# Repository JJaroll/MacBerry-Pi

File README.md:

# MacBerry Pi G3 · en español

[-9aa0a6?logo=apple&logoColor=white)](docs/guia_macberry_pi.md)

Convierte un **iMac G3 DV (slot loading)** en un equipo moderno: una **Raspberry Pi 5** dentro de la carcasa que usa el **tubo CRT original como monitor VGA**, con sus altavoces y su botón de encendido. Reversible: no hay que cortar nada del iMac.

Este repositorio reúne **la documentación en español**, las **tres placas del proyecto original traducidas**, un **PCB master unificado** que reemplaza el cableado entre ellas, y **visores 3D** (HTML autónomo y STL) para revisarlo todo sin instalar nada.

> **Proyecto original:** [`qbancoffee/imac_g3_ivad_board_init`](https://github.com/qbancoffee/imac_g3_ivad_board_init) (LGPL-3.0), de **Rocky Hill (qbancoffee)**. Este trabajo es derivado de él: ver [CREDITOS.md](CREDITOS.md).

> ⚠️ **Riesgo:** el CRT retiene carga aunque esté desenchufado, el bisel interior es muy frágil y la estática daña la electrónica. Hazlo bajo tu propia responsabilidad.

## Por dónde empezar

**Recomendado:** abre la [**guía interactiva paso a paso**](https://jjaroll.github.io/MacBerry-Pi/) (plan personalizado, cables, jumpers, calibración, diagnóstico y descargas). Los archivos viven en `index.html` y `sitio/`.

O lee los documentos:

1. Lee la [**Guía de cableado con Raspberry Pi 5**](docs/guia_cableado_pi5.md) (pines verificados, jumpers, alimentación y pruebas) y, como contexto, la [guía completa de implementación](docs/guia_macberry_pi.md).
2. Abre los visores de [`visores/`](visores) con doble clic para ver el montaje.
3. Elige el camino de construcción: [placas individuales o PCB master](#placas-individuales-o-master).

## Estructura

```
Macberri Pi/
├─ README.md · CREDITOS.md · LICENSE
├─ docs/
│  ├─ guia_macberry_pi.md              guía completa de implementación (traducción y adaptación)
│  ├─ guia_cableado_pi5.md             cableado, pines verificados, jumpers y pruebas con Pi 5
│  ├─ informe_master_v5.md             informe del PCB master
│  ├─ traducciones/                    README y notas del proyecto original, en español
│  └─ historial/                       informes de versiones anteriores (fusión, v2–v4)
├─ hardware/
│  ├─ placas_individuales/             J20, J22 y Down Converter: KiCad con serigrafía en español y firma,
│  │                                   esquemático_es/ (esquema traducido) y fabricacion/ (Gerber, BOM, iBOM)
│  ├─ master_pcb/                      master v5: KiCad, Gerber, DXF/SVG 1:1, vistas previas
│  └─ contribuciones_rudy/             HAT RPiG3iMac y breakout J20 de Rudy (reng.ca), KiCad + Gerber
├─ firmware/                           Arduino (inicialización IVAD, simulador EDID), init_ivad.py y edid.bin
├─ utilidades/                         ImacG3DVDisplayProperties (calibración de pantalla, Java)
├─ visores/                            HTML autónomos: 3D, cableado sin master, cableado con master, visor STL
├─ stl/
│  ├─ pcb/                             master y placas individuales en STL (1:1, 1,6 mm)
│  ├─ rpi_mount/                       soporte de la Pi (Rudy, reng.ca)
│  └─ bezel/                           bisel interior de Anthony Bernaert (17 STL, CC BY-NC 4.0)
└─ originales/                         de qbancoffee, sin modificar: esquemas PDF, proyecto KiCad (con modelos 3D), imágenes (fotos a 1600 px),
                                       raw_data (capturas I²C y EDID) y surfacemount_version (SMD, en desarrollo)
```

## Visores

| Archivo | Para qué sirve |
|---|---|
| [`visores/visor3d_pcbs.html`](visores/visor3d_pcbs.html) | **Todo en 3D**: master con las 3 placas en sus bolsillos, la Pi 5 con su case, cables cortos, rutas, logos y despiece |
| [`visores/cableado_sin_master.html`](visores/cableado_sin_master.html) | **Sistema de cables sin master**: 19 cables punto a punto entre placas, amplificador y GPIO de la Pi |
| [`visores/cableado_con_master.html`](visores/cableado_con_master.html) | **Sistema con master**: 20 rutas de cobre y cables cortos entre cada bornera y su terminal |
| [`visores/visor_inner_bezel.html`](visores/visor_inner_bezel.html) | **Visor STL del inner bezel (bisel interior)**: las 17 piezas embebidas, ensamblaje, vista explosionada, orden de montaje, cotas, medidas, piezas con soportes sobre la cama y descarga en .zip |

Funcionan con doble clic y sin internet (three.js y los STL van incrustados). Solo las tipografías de algunos visores vienen de Google Fonts; sin conexión se usa la del sistema.

## BOM interactivo (iBOM)

Cada placa tiene su BOM interactivo en español: lista de componentes, posición en la placa (cara frontal y trasera), pistas, zonas y serigrafía. Se abren con doble clic. Colores base: J20 azul, J22 púrpura, Down Converter negro y master verde.

| Placa | iBOM |
|---|---|
| PCB master v5 | [`hardware/master_pcb/ibom_master.html`](hardware/master_pcb/ibom_master.html) |
| J20 · video y ATmega | [`hardware/placas_individuales/J20_video/ibom_es.html`](hardware/placas_individuales/J20_video/ibom_es.html) |
| J22 · frontal y audio | [`hardware/placas_individuales/J22_frontal_audio/ibom_es.html`](hardware/placas_individuales/J22_frontal_audio/ibom_es.html) |
| Down Converter | [`hardware/placas_individuales/DownConverter/ibom_es.html`](hardware/placas_individuales/DownConverter/ibom_es.html) |

Se generan con [`utilidades/generar_ibom/`](utilidades/generar_ibom), sin KiCad. Los iBOM originales (en inglés) siguen en `originales/` y en `fabricacion/bom/`.

## Placas individuales o master

- **Placas individuales** ([`hardware/placas_individuales/`](hardware/placas_individuales)): el diseño original con sus borneras y el cableado de siempre. Es lo más sencillo de fabricar y ensamblar (todo *through-hole*). Serigrafía y comentarios traducidos al español y firma `JJaroll.dev`.
- **PCB master** ([`hardware/master_pcb/`](hardware/master_pcb)): una sola placa con la forma de la placa lógica 820-1131-A. Las 3 placas individuales se atornillan en bolsillos (holgura 0,3 mm) y el master las une con pistas, con huecos para la Raspberry Pi 5 con su case y un módulo PAM8403. Ver [`docs/informe_master_v5.md`](docs/informe_master_v5.md).

**Estado del master:** 20 de 20 conexiones verificadas con script propio y sin cortocircuitos. **No se ha ejecutado DRC en KiCad ni se ha fabricado.** Lee la sección «Antes de fabricar» del informe. Las medidas salen de fotos y de un *cutting mat*: verifica con calibre.

## Qué cambié respecto al original

- Serigrafía y comentarios de las 3 placas traducidos al español (las señales técnicas como `SDA`, `GND`, `MOSI` se mantienen).
- Firma `JJaroll.dev` y créditos en el bloque de título de cada placa.
- Documentación del proyecto original y guía MacBerry Pi (Raspberry Pi 5) en español.
- PCB master, visores, mapas de cableado y STL nuevos.

Las placas individuales incluyen su Gerber en español listo para fabricar (`fabricacion/*_gerber.zip`), con DRC revisado. Los Gerber originales (serigrafía en inglés) siguen en [`originales/proyecto_kicad_original/`](originales/proyecto_kicad_original).

## Contribuir

Issues y pull requests son bienvenidos: errores de traducción, medidas verificadas con calibre, resultados de DRC o fabricación del master.

## Licencia

[LGPL-3.0](LICENSE), igual que el proyecto original. Lo derivado se publica con la misma licencia.

**Excepción:** los STL del bisel interior (`stl/bezel/`) son obra de Anthony Bernaert bajo **[CC BY-NC 4.0](stl/bezel/LICENSE_CC-BY-NC-4.0.md)** (atribución, **solo uso no comercial**) y no están cubiertos por la LGPL. Ver [`stl/bezel/LEEME.md`](stl/bezel/LEEME.md).

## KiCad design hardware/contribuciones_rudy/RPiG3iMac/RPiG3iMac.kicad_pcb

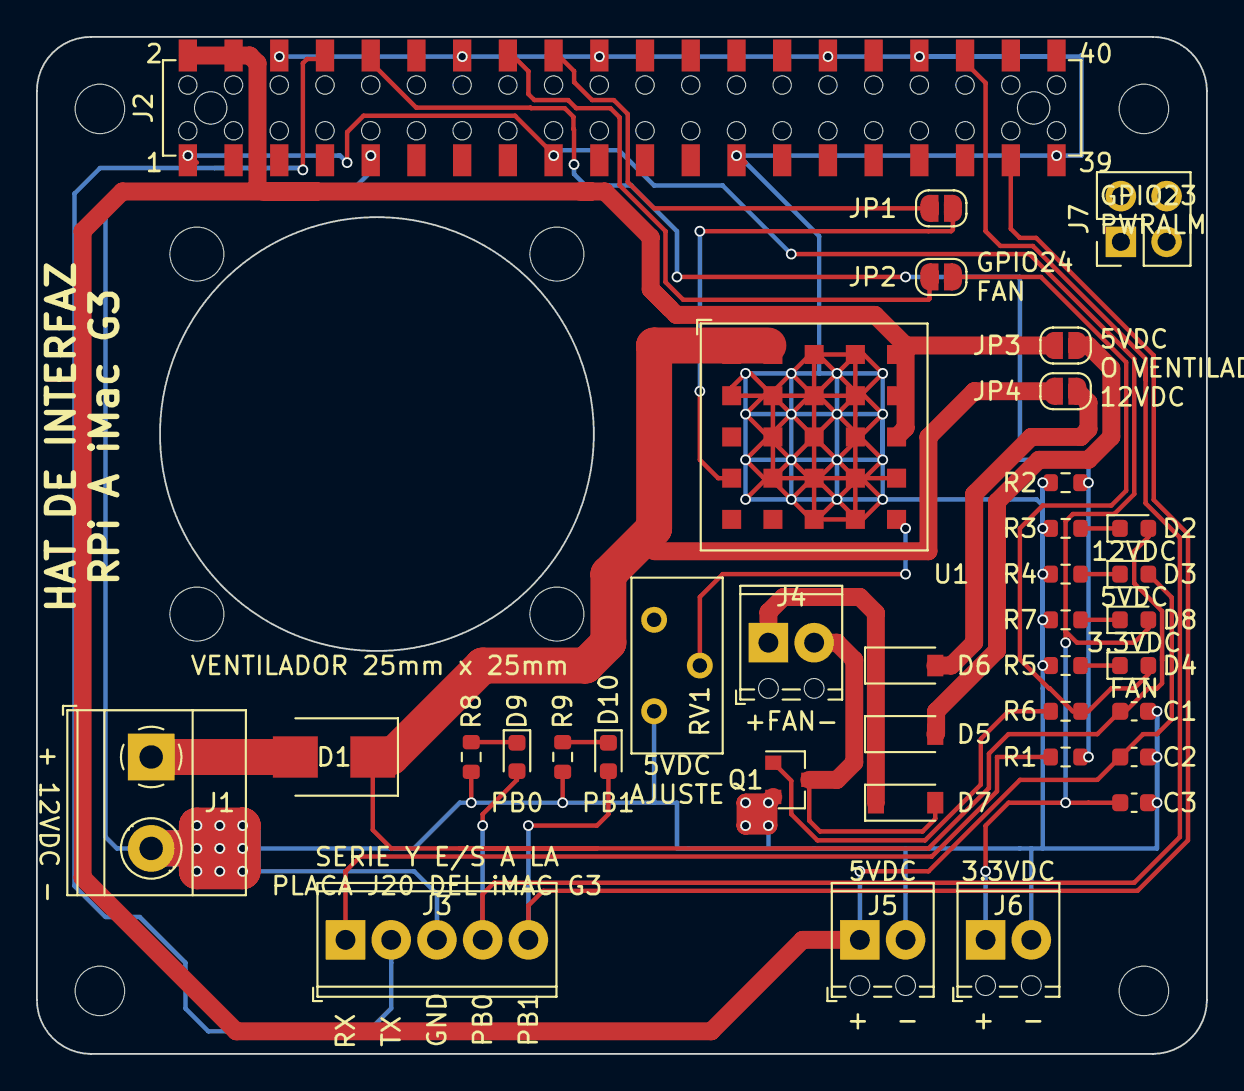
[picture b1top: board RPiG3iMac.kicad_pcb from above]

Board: 2 copper layers, 65.0 x 56.5 mm, 40 parts (0 on the bottom side), 26 nets.

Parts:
 : MountingHole_3mm
 #2,  #3,  #4: MountingHole_3mm
C1: 10uF 25V; C_0603_1608Metric
C2, C3: 22uF 10V; C_0603_1608Metric
D1: 40V 3A; D_SMB
D2: 12VDC; LED_0603_1608Metric
D3: 5VDC; LED_0603_1608Metric
D4: FAN; LED_0603_1608Metric
D5, D6, D7: 100V 150mA; D_SOD-123
D8, D9, D10: 3.3VDC; LED_0603_1608Metric
J1: 12VDC IN; TerminalBlock_Phoenix_MKDS-1,5-2-5.08_1x02_P5.08mm_Horizont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
J2: RPi; Harwin_M20-7812045_2x20_P2.54mm_Vertical_rpi
J3: SERIAL TO iMAC G3 J20 BOARD; TerminalBlock_Phoenix_MPT-0,5-5-2.54_1x05_P2.54mm_Horizontal
J4: FAN; TerminalBlock_Phoenix_MPT-0,5-2-2.54_1x02_P2.54mm_Horizontal
J5: 5VDC OUT; TerminalBlock_Phoenix_MPT-0,5-2-2.54_1x02_P2.54mm_Horizontal
J6: 3.3V DC OUT; TerminalBlock_Phoenix_MPT-0,5-2-2.54_1x02_P2.54mm_Horizontal
J7: RPi POE Header; PinHeader_2x02_P2.54mm_Vertical
JP1: GPIO23 PWR STATUS; SolderJumper-2_P1.3mm_Open_RoundedPad1.0x1.5mm
JP2: GPIO24 TO FAN; SolderJumper-2_P1.3mm_Open_RoundedPad1.0x1.5mm
JP3: 5VDC; SolderJumper-2_P1.3mm_Open_RoundedPad1.0x1.5mm
JP4: 12VDC; SolderJumper-2_P1.3mm_Open_RoundedPad1.0x1.5mm
Q1: BC817; SOT-23
R1: 1K0; R_0603_1608Metric
R2, R3: 2K0; R_0603_1608Metric
R4, R6: 470; R_0603_1608Metric
R5, R7, R8, R9: 220; R_0603_1608Metric
RV1: 5M0; Potentiometer_Bourns_3296Y_Vertical
U1: RPM5.0-3.0; Converter_DCDC_RECOM_RPMx.x-x.0

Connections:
+3V3: C3.1, D8.2, J2.1, J2.17, J6.1
+5V: C2.1, D3.2, J2.2, J2.4, J5.1, JP3.1, U1.A5, U1.B5, U1.C5
+12V: C1.1, D1.1, D2.2, JP4.1, U1.A1, U1.A2
/PB0_FROM_J20: D9.2, J2.36, J3.4
/PB1_FROM_J20: D10.2, J2.37, J3.5
/RX_FROM_J20: J2.8, J3.2
/TX_FROM_J20_(5V): J3.1, R1.1
GND: C1.2, C2.2, C3.2, J1.2, J2.6, J2.9, J2.14, J2.20, J2.25, J2.30, J2.34, J2.39, J3.3, J5.2, J6.2, Q1.2, R2.2, R3.2, R4.2, R5.2, R7.2, R8.2, R9.2, RV1.3, U1.A3, U1.A4, U1.B1, U1.B2, U1.B3, U1.B4, U1.C2, U1.C3, U1.C4, U1.D2, U1.D3, U1.D4, U1.D5, U1.E3, U1.E4
unnamed: D1.2, J1.1
unnamed: D2.1, R3.1
unnamed: D3.1, R4.1
unnamed: D4.1, R5.1
unnamed: D4.2, JP2.1, R6.2
unnamed: D5.1, D6.1, D7.1, J4.1
unnamed: D5.2, JP3.2
unnamed: D6.2, JP4.2
unnamed: D7.2, J4.2, Q1.3
unnamed: D8.1, R7.1
unnamed: D9.1, R8.1
unnamed: D10.1, R9.1
unnamed: J2.10, R1.2, R2.1
unnamed: J2.16, JP2.2
unnamed: J2.18, JP1.2
unnamed: JP1.1, U1.D1
unnamed: Q1.1, R6.1
unnamed: RV1.2, U1.E5

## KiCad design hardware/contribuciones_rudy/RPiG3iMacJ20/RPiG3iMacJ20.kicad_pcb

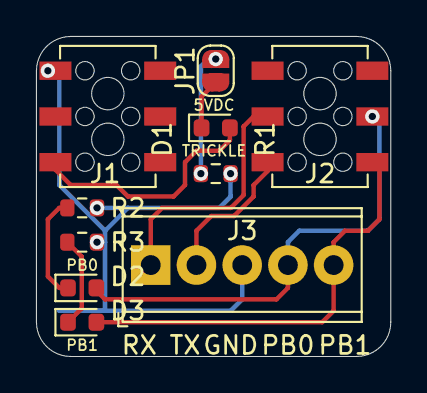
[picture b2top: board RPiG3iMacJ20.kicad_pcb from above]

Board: 2 copper layers, 19.7 x 17.8 mm, 10 parts (0 on the bottom side), 10 nets.

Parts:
D1, D2, D3: LED; LED_0603_1608Metric
J1, J2: Conn_02x03_Odd_Even; Harwin_M20-7810345_2x03_P2.54mm_Vertical
J3: Screw_Terminal_01x05; TerminalBlock_Phoenix_MPT-0,5-5-2.54_1x05_P2.54mm_Horizontal
JP1: SolderJumper_2_Open; SolderJumper-2_P1.3mm_Open_RoundedPad1.0x1.5mm
R1: 470; R_0603_1608Metric
R2, R3: 220; R_0603_1608Metric

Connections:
+5V: D1.2, J1.5
GND: J1.1, J3.3, R1.2, R2.2, R3.2
unnamed: D1.1, JP1.1
unnamed: D2.1, R2.1
unnamed: D2.2, J2.4, J3.4
unnamed: D3.1, R3.1
unnamed: D3.2, J2.6, J3.5
unnamed: J2.3, J3.1
unnamed: J2.5, J3.2
unnamed: JP1.2, R1.1

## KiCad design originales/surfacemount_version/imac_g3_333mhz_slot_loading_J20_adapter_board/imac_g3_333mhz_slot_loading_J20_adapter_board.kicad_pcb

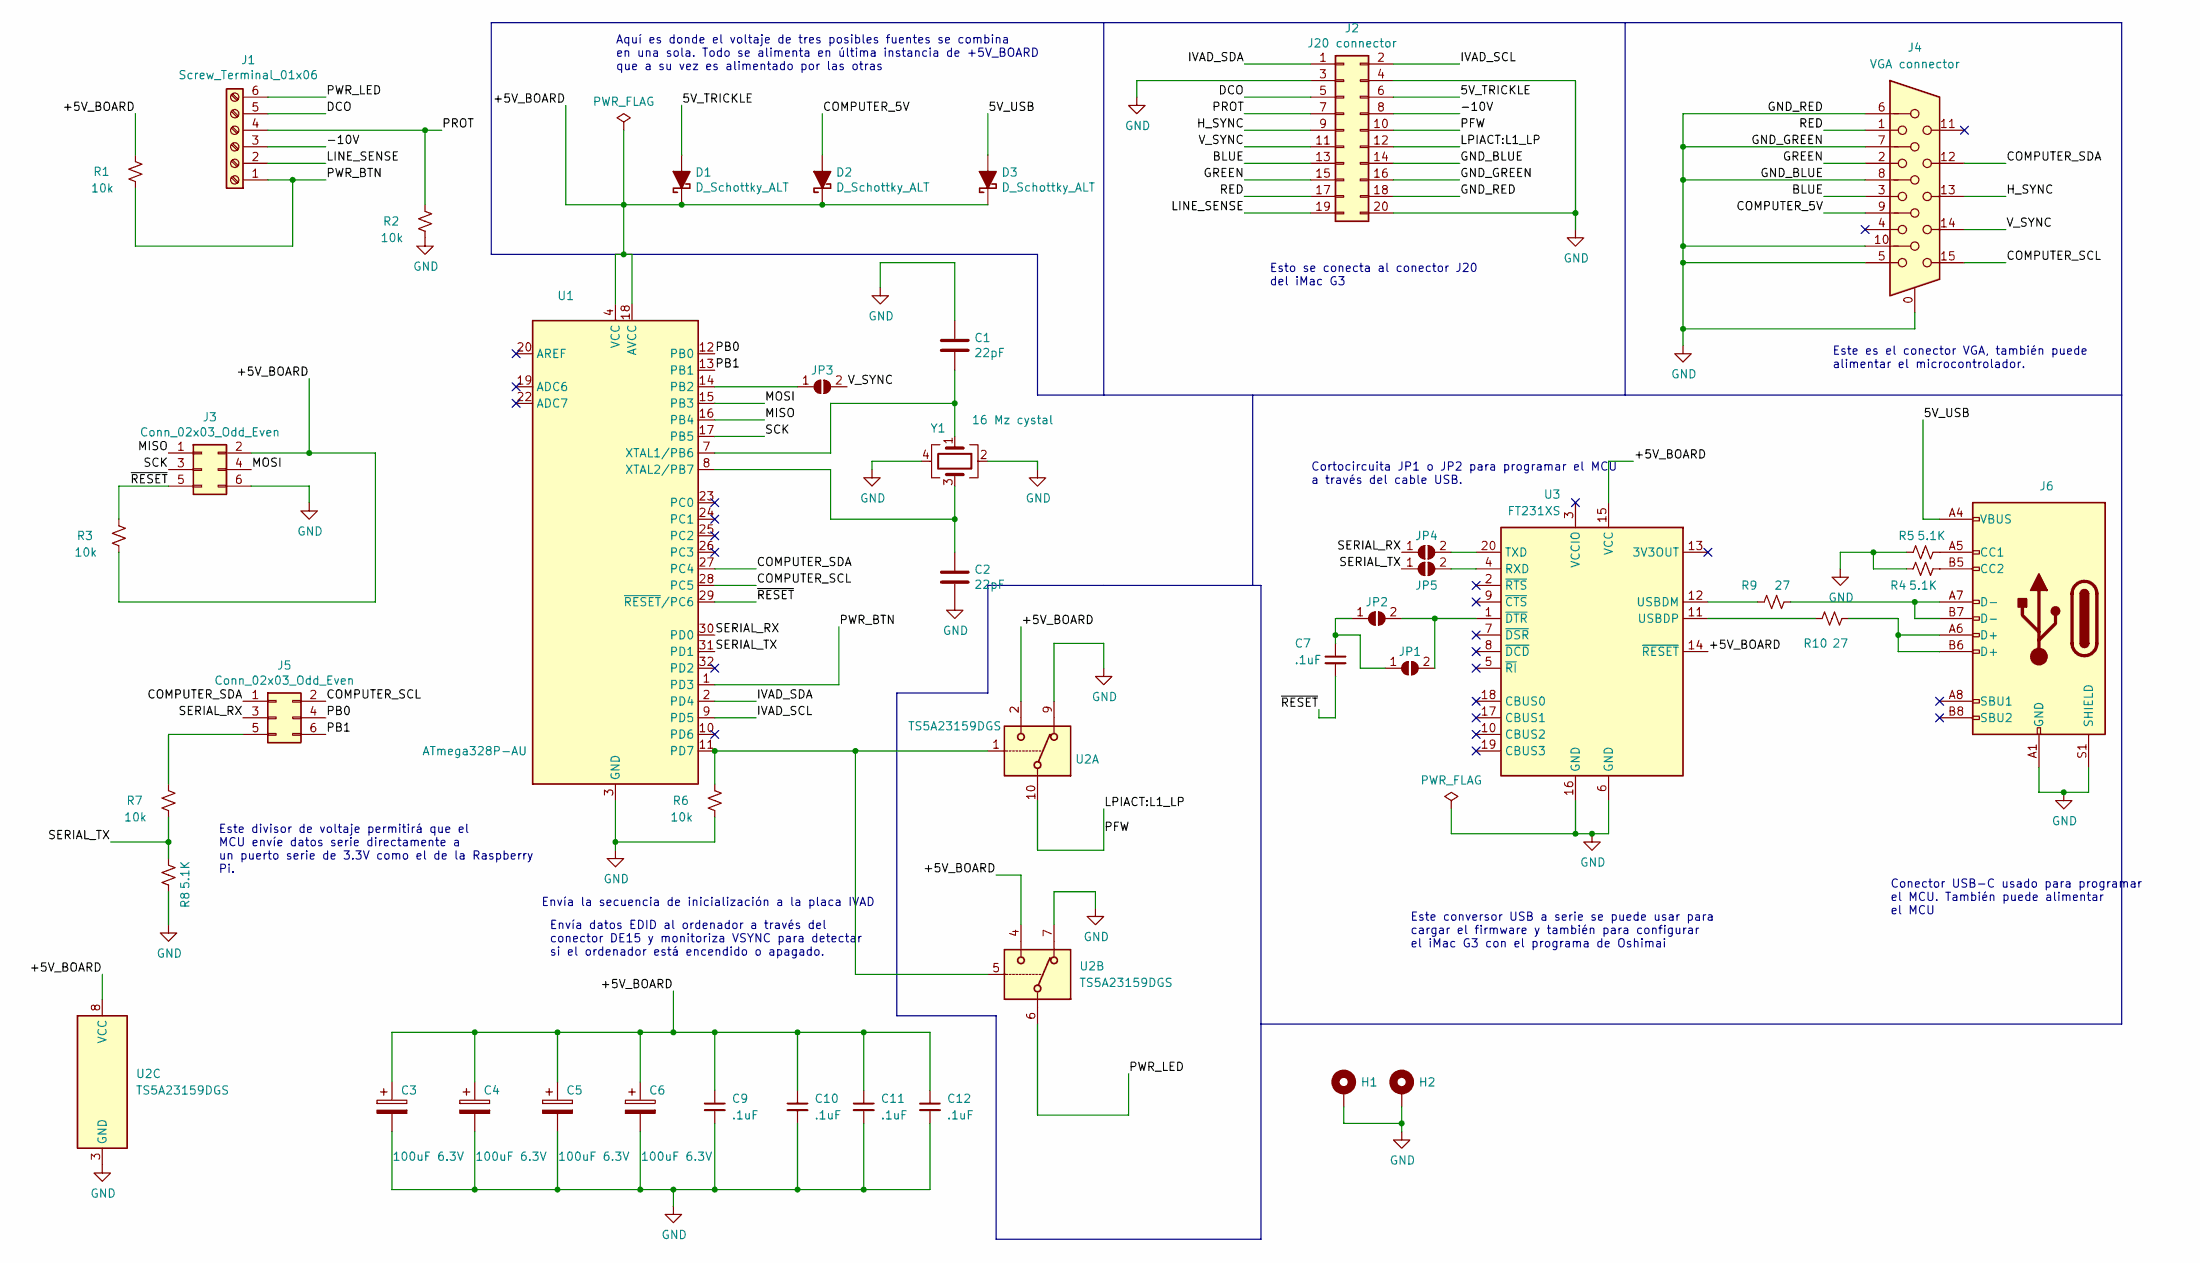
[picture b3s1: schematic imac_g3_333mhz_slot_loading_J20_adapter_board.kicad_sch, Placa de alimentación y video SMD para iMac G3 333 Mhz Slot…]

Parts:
C1, C2: 22pF; C_0805_2012Metric_Pad1.18x1.45mm_HandSolder; Manufacturer part# CL21C220JBANNNC
C3, C4, C5, C6: 100uF 6.3V; CP_EIA-3528-21_Kemet-B_Pad1.50x2.35mm_HandSolder; Manufacturer part# TAJB107K006RNJ
C7, C9, C10, C11, C12: .1uF; C_0805_2012Metric_Pad1.18x1.45mm_HandSolder; Manufacturer part# CL21B104KCFNNNE
D1, D2, D3: D_Schottky_ALT; D_SOD-123; Manufacturer part# B5819W SL
H1, H2: MountingHole_Pad; MountingHole_3.5mm_Pad
J1: Screw_Terminal_01x06; TerminalBlock_Phoenix_PT-1,5-6-5.0-H_1x06_P5.00mm_Horizontal; Part# 277-1581-ND
J2: J20 connector; PinHeader_2x10_P2.54mm_Vertical; Part# SAM1068-10-ND
J3: Conn_02x03_Odd_Even; PinHeader_2x03_P2.54mm_Vertical; Part# 732-5394-ND
J4: VGA connector; DSUB-15-HD_Female_Horizontal_P2.29x1.98mm_EdgePinOffset8.35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; Manufacturer part# Z-SUBHRBF707A000
J5: Conn_02x03_Odd_Even; PinHeader_2x03_P2.54mm_Vertical; Part# 609-3234-ND
J6: USB_C_Receptacle_USB2.0; USB_C_Receptacle_G-Switch_GT-USB-7010ASV; Manufacturer part# TYPE C-DB-108PWB
JP1: SolderJumper_2_Open; PinHeader_1x02_P2.54mm_Vertical
JP2, JP3, JP4, JP5: SolderJumper_2_Open; SolderJumper-2_P1.3mm_Open_RoundedPad1.0x1.5mm
R1, R2, R3, R6, R7: 10k; R_0805_2012Metric_Pad1.20x1.40mm_HandSolder; Manufacturer part# 0805W8F1002T5E
R4, R5, R8: 5.1K; R_0805_2012Metric_Pad1.20x1.40mm_HandSolder; Manufacturer part# 0805W8F5101T5E
R9, R10: 27; R_0805_2012Metric_Pad1.20x1.40mm_HandSolder; Manufacturer part# 0805W8F270JT5E
U1: ATmega328P-AU; TQFP-32_7x7mm_P0.8mm; Manufacturer part# ATMEGA328P-AU
U2: TS5A23159DGS; VSSOP-10_3x3mm_P0.5mm; Manufacturer part# TS5A23159DGSR
U3: FT231XS; SSOP-20_3.9x8.7mm_P0.635mm; Manufacturer part# FT231XS-R
Y1: 16 Mz cystal; Crystal_SMD_3225-4Pin_3.2x2.5mm_HandSoldering; Manufacturer part# X322516MLB4SI

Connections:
/5V_TRICKLE: D1.2 (A), J2.6
/5V_USB: D3.2 (A), J6.A4 (VBUS), J6.A9 (VBUS), J6.B4 (VBUS), J6.B9 (VBUS)
/+5V_BOARD: C3.1, C4.1, C5.1, C6.1, C9.1, C10.1, C11.1, C12.1, D1.1 (K), D2.1 (K), D3.1 (K), J3.2, R1.2, R3.1, U1.4 (VCC), U1.6 (VCC), U1.18 (AVCC), U2.2, U2.4, U2.8 (VCC), U3.14 (~RESET), U3.15 (VCC)
/-10V: J1.3, J2.8
/BLUE: J2.13, J4.3
/COMPUTER_5V: D2.2 (A), J4.9
/COMPUTER_SCL: J4.15, J5.2, U1.28 (PC5)
/COMPUTER_SDA: J4.12, J5.1, U1.27 (PC4)
/DCO: J1.5, J2.5
/GREEN: J2.15, J4.2
/H_SYNC: J2.9, J4.13
/IVAD_SCL: J2.2, U1.9 (PD5)
/IVAD_SDA: J2.1, U1.2 (PD4)
/LINE_SENSE: J1.2, J2.19
/LPIACT:L1_LP: J2.10, J2.12, U2.10
/MISO: J3.1, U1.16 (PB4)
/MOSI: J3.4, U1.15 (PB3)
/PB0: J5.4, U1.12 (PB0)
/PB1: J5.6, U1.13 (PB1)
/PROT: J1.4, J2.7, R2.2
/PWR_BTN: J1.1, R1.1, U1.1 (PD3)
/PWR_LED: J1.6, U2.6
/RED: J2.17, J4.1
/SCK: J3.3, U1.17 (PB5)
/SERIAL_RX: J5.3, JP4.1 (A), U1.30 (PD0)
/SERIAL_TX: JP5.1 (A), R7.1, R8.1, U1.31 (PD1)
/V_SYNC: J2.11, J4.14, JP3.2 (B)
/~RESET: C7.2, J3.5, R3.2, U1.29 (~RESET/PC6)
GND: C1.1, C2.2, C3.2, C4.2, C5.2, C6.2, C9.2, C10.2, C11.2, C12.2, H1.1, H2.1, J2.3, J2.4, J2.14, J2.16, J2.18, J2.20, J3.6, J4.0, J4.5, J4.6, J4.7, J4.8, J4.10, J6.A1 (GND), J6.A12 (GND), J6.B1 (GND), J6.B12 (GND), J6.S1 (SHIELD), R2.1, R4.2, R5.2, R6.1, R8.2, U1.3 (GND), U1.5 (GND), U1.21 (GND), U2.3 (GND), U2.7, U2.9, U3.6 (GND), U3.16 (GND), Y1.2, Y1.4
unnamed: J5.5, R7.2
unnamed: J6.A5 (CC1), R5.1
unnamed: J6.B5 (CC2), R4.1
unnamed: J6.A6 (D+), J6.B6 (D+), R10.1
unnamed: J6.A7 (D-), J6.B7 (D-), R9.1
unnamed: C7.1, JP1.1 (A), JP2.1 (A)
unnamed: JP1.2 (B), JP2.2 (B), U3.1 (~DTR)
unnamed: JP3.1 (A), U1.14 (PB2)
unnamed: JP4.2 (B), U3.20 (TXD)
unnamed: JP5.2 (B), U3.4 (RXD)
unnamed: R6.2, U1.11 (PD7), U2.1, U2.5
unnamed: C1.2, U1.7 (XTAL1/PB6), Y1.1
unnamed: C2.1, U1.8 (XTAL2/PB7), Y1.3
unnamed: R9.2, U3.12 (USBDM)
unnamed: R10.2, U3.11 (USBDP)

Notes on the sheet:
Conector USB-C usado para programar el MCU. También puede alimentar el MCU
Este es el conector VGA, también puede alimentar el microcontrolador.
Aquí es donde el voltaje de tres posibles fuentes se combina en una sola. Todo se alimenta en última instancia de +5V_BOARD que a su vez es alimentado por las otras
Envía datos EDID al ordenador a través del conector DE15 y monitoriza VSYNC para detectar si el ordenador está encendido o apagado.
Esto se conecta al conector J20 del iMac G3
Este conversor USB a serie se puede usar para cargar el firmware y también para configurar el iMac G3 con el programa de Oshimai
Cortocircuita JP1 o JP2 para programar el MCU a través del cable USB.
Este divisor de voltaje permitirá que el MCU envíe datos serie directamente a un puerto serie de 3.3V como el de la Raspberry Pi.
Envía la secuencia de inicialización a la placa IVAD

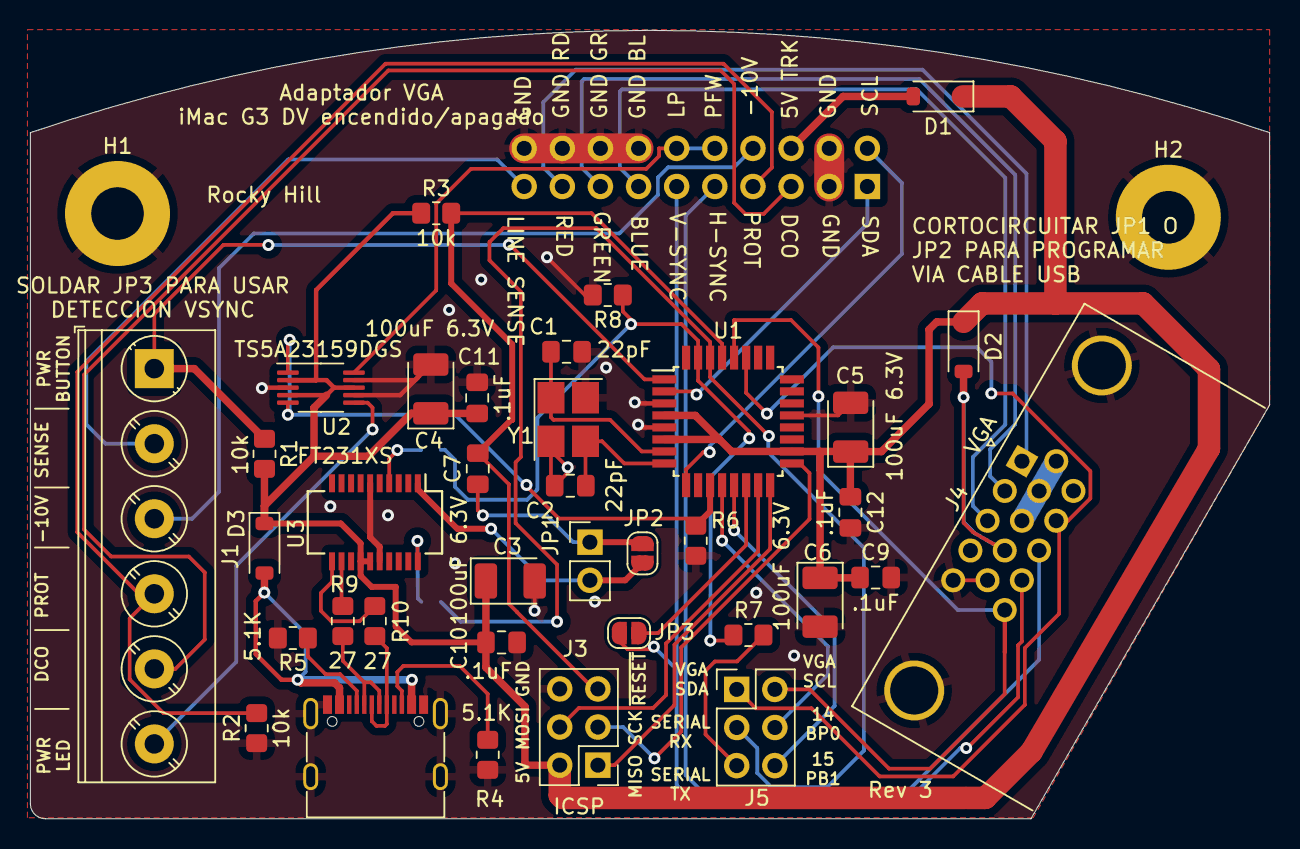
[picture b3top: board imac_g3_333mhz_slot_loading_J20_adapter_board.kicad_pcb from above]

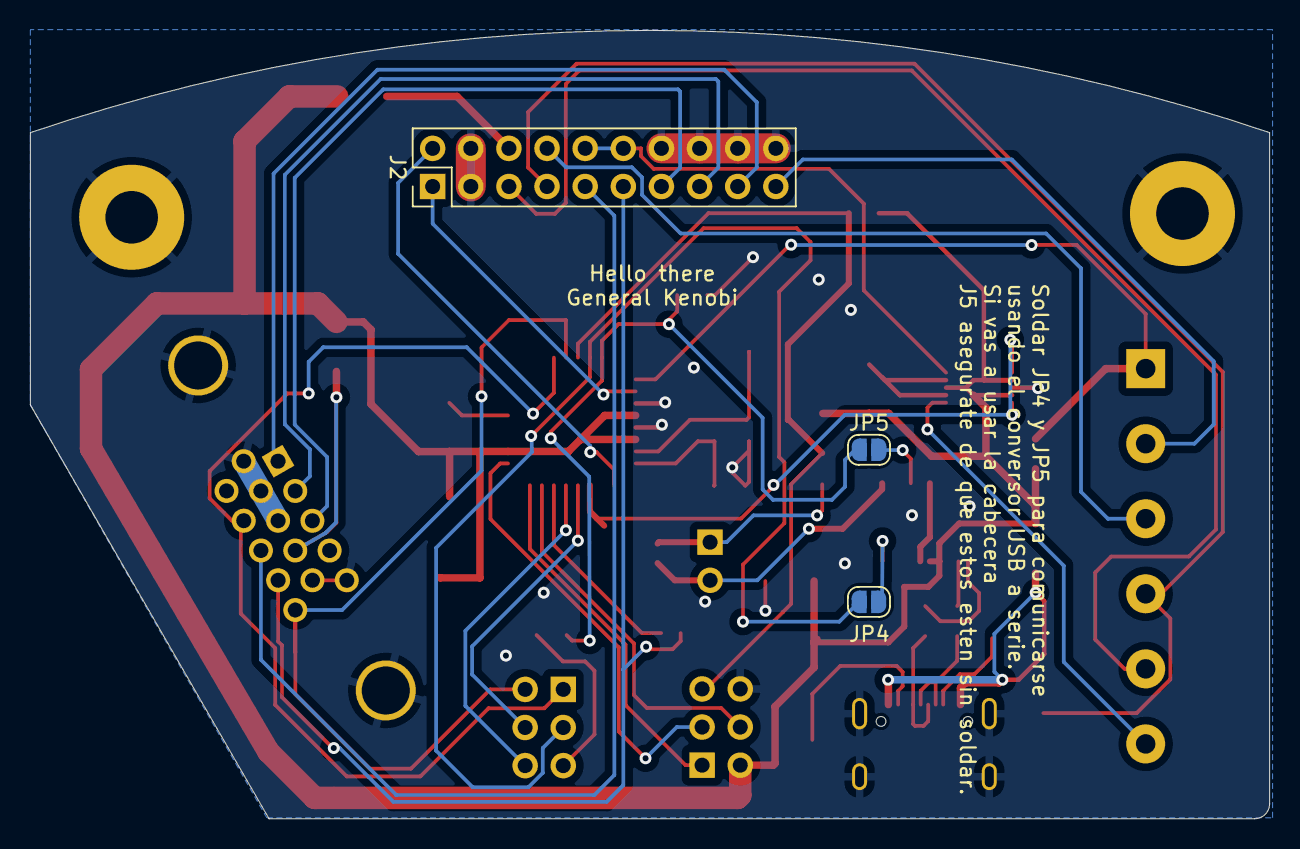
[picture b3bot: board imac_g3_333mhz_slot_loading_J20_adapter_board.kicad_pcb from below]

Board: 2 copper layers, 82.5 x 52.5 mm, 41 parts (3 on the bottom side), 44 nets.

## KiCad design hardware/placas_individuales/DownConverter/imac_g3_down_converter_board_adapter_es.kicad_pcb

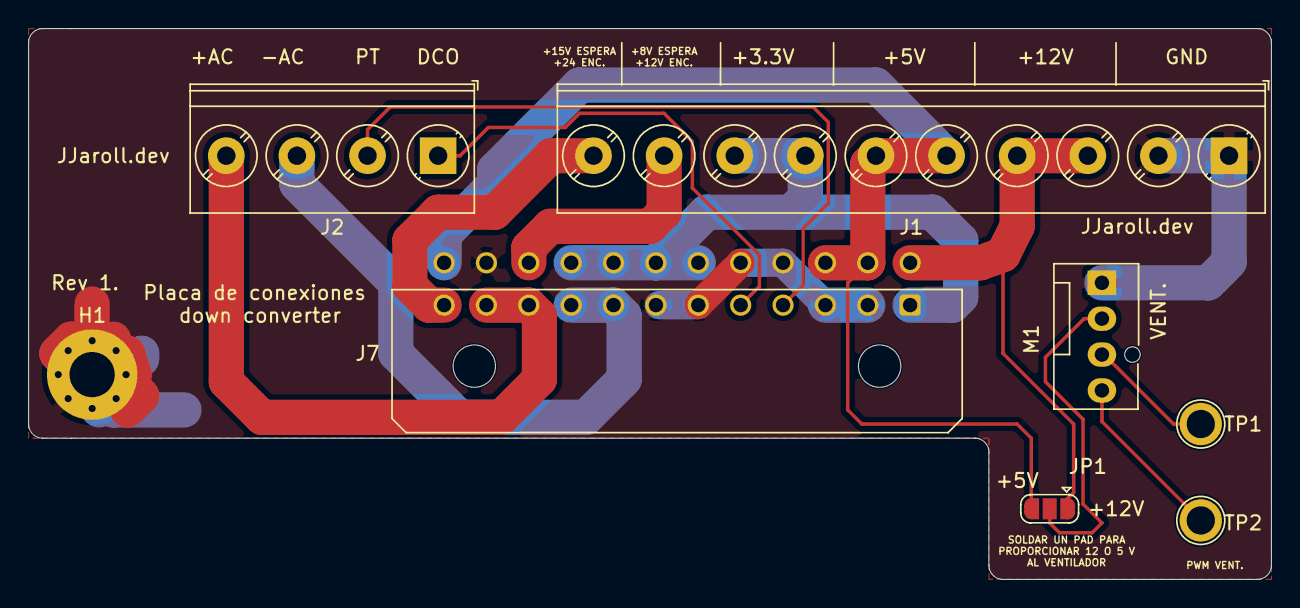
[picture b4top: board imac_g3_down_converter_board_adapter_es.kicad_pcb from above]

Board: 2 copper layers, 88.0 x 39.0 mm, 8 parts (0 on the bottom side), 13 nets.

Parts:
H1: MountingHole_Pad; MountingHole_3.2mm_M3_Pad_Via
J1: Screw_Terminal_01x10; TerminalBlock_Phoenix_PT-1,5-10-5.0-H_1x10_P5.00mm_Horizont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
J2: Screw_Terminal_01x04; TerminalBlock_Phoenix_PT-1,5-4-5.0-H_1x04_P5.00mm_Horizontal
J7: Conn_02x12_Top_Bottom; Molex_Micro-Fit_3.0_43045-2400_2x12_P3.00mm_Horizontal
JP1: SolderJumper_3_Open; SolderJumper-3_P1.3mm_Open_RoundedPad1.0x1.5mm
M1: Fan_Tacho_PWM; FanPinHeader_1x04_P2.54mm_Vertical
TP1, TP2: TestPoint; TestPoint_Plated_Hole_D2.0mm

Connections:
/+3.3V: J1.7, J1.8, J7.1, J7.18, J7.19, J7.20, J7.21
/+5V: J1.5, J1.6, J7.14, J7.15, J7.24, JP1.3
/+8V_STANDBY_+12V_ON: J1.9, J7.22
/+12V: J1.3, J1.4, J7.13, JP1.1
/+15V_STANDBY_+24V_ON: J1.10, J7.12
/+AC: J2.4, J7.10, J7.11
/-AC: J2.3, J7.8, J7.9
/DCO: J2.1, J7.5
/GND: H1.1, J1.1, J1.2, J7.2, J7.3, J7.6, J7.7, J7.16, J7.17, J7.23, M1.1
/PT: J2.2, J7.4
/PWM: M1.4, TP2.1
/TACHO: M1.3, TP1.1
unnamed: JP1.2, M1.2

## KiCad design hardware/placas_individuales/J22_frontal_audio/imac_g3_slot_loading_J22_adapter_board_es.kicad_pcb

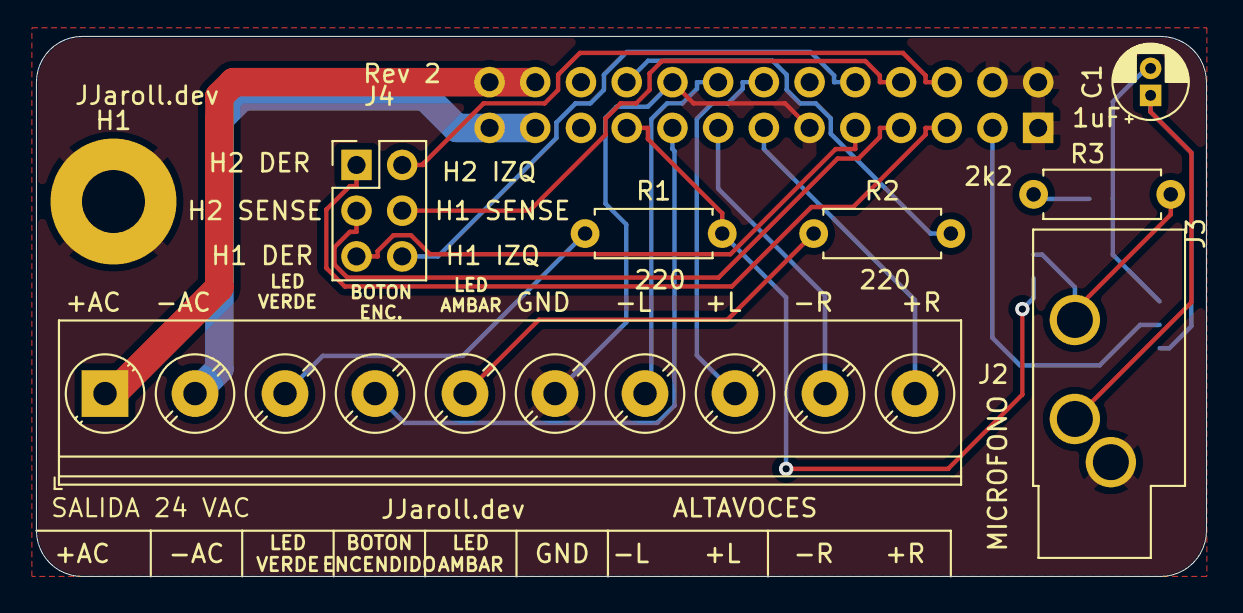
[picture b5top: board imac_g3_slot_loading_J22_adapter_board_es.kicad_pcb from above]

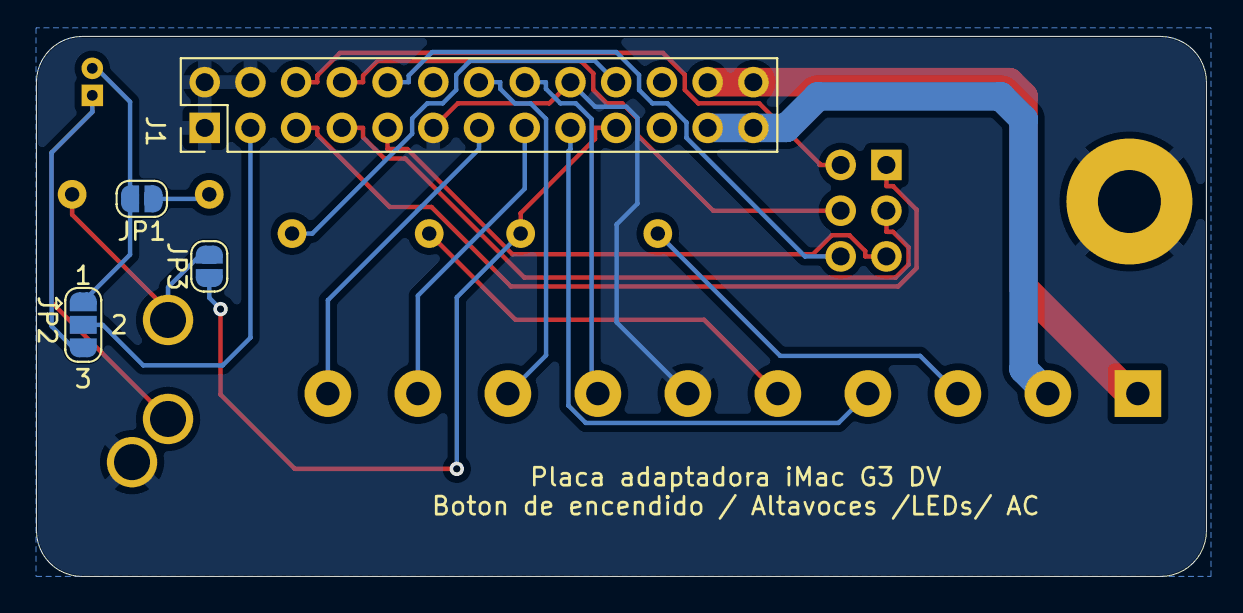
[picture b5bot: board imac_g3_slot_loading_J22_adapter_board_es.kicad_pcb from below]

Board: 2 copper layers, 65.0 x 30.0 mm, 12 parts (4 on the bottom side), 23 nets.

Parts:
C1: 1uF; CP_Radial_D4.0mm_P1.50mm
H1: MountingHole_Pad; MountingHole_3.5mm_Pad
J1: Conn_02x13_Odd_Even; PinHeader_2x13_P2.54mm_Vertical
J2: Screw_Terminal_01x10; TerminalBlock_Phoenix_PT-1,5-10-5.0-H_1x10_P5.00mm_Horizont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
J3: AudioJack3; Jack_3.5mm_CUI_SJ1-3533NG_Horizontal_CircularHoles
J4: Conn_02x03_Odd_Even; PinHeader_2x03_P2.54mm_Vertical
JP1, JP3: SolderJumper_2_Open; SolderJumper-2_P1.3mm_Open_RoundedPad1.0x1.5mm
JP2: SolderJumper_3_Open; SolderJumper-3_P1.3mm_Open_RoundedPad1.0x1.5mm
R1, R2: 220; R_Axial_DIN0207_L6.3mm_D2.5mm_P7.62mm_Horizontal
R3: 2.2k; R_Axial_DIN0207_L6.3mm_D2.5mm_P7.62mm_Horizontal

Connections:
/+AC: J1.24, J1.26, J2.1
/+AMBER_LED: J1.20, R2.2
/+GREEN_LED: J1.19, JP3.1, R1.2
/+LEFT_SPEAKER: J1.14, J2.8
/+MICROPHONE: J1.3, JP2.2
/+RIGHT_SPEAKER: J1.13, J2.10
/-AC: J1.23, J1.25, J2.2
/-LEFT_SPEAKER: J1.16, J2.7
/-RIGHT_SPEAKER: J1.15, J2.9
/HEADPHONE_1_LEFT: J1.10, J4.6
/HEADPHONE_1_RIGHT: J1.9, J4.5
/HEADPHONE_1_SENSE: J1.8, J4.4
/HEADPHONE_2_LEFT: J1.6, J4.2
/HEADPHONE_2_RIGHT: J1.5, J4.1
/HEADPHONE_2_SENSE: J1.7, J4.3
/MICROPHONE_POWER: J3.R, JP3.2, R3.2
/POWER_BUTTON: J1.17, J2.4
GNDREF: H1.1, J1.1, J1.2, J1.4, J1.11, J1.18, J2.6, J3.S
unnamed: C1.1, J3.T, JP2.3
unnamed: C1.2, JP1.2, JP2.1
unnamed: J2.3, R1.1
unnamed: J2.5, R2.1
unnamed: JP1.1, R3.1

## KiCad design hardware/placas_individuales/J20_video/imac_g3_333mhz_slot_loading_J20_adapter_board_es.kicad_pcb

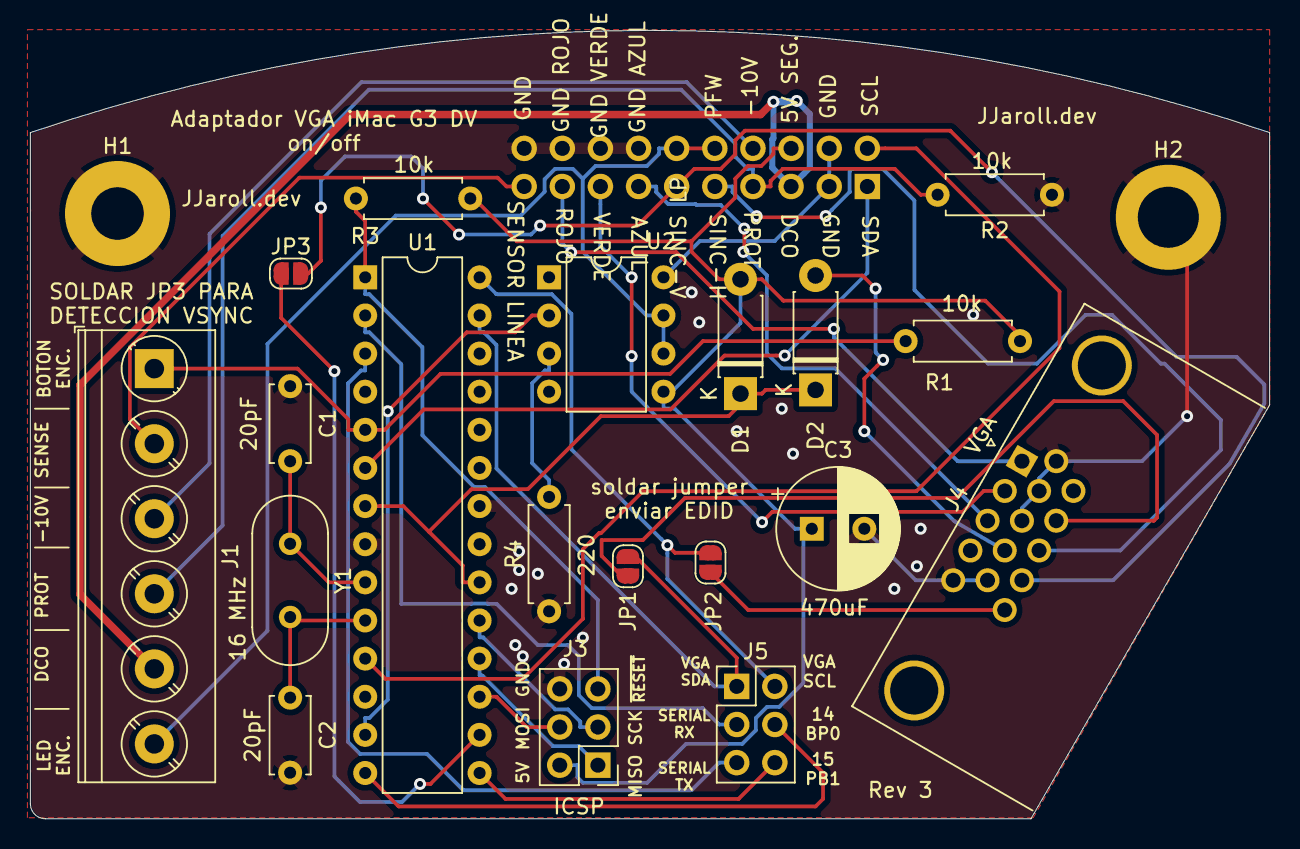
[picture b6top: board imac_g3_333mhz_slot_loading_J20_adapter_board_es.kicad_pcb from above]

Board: 2 copper layers, 82.5 x 52.5 mm, 22 parts (1 on the bottom side), 34 nets.

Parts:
C1, C2: 22pF; C_Disc_D5.0mm_W2.5mm_P5.00mm
C3: 470uF; CP_Radial_D8.0mm_P3.50mm
D1, D2: D_Schottky_ALT; D_DO-41_SOD81_P7.62mm_Horizontal
H1, H2: MountingHole_Pad; MountingHole_3.5mm_Pad
J1: Screw_Terminal_01x06; TerminalBlock_Phoenix_PT-1,5-6-5.0-H_1x06_P5.00mm_Horizontal
J2: Conn_02x10_Odd_Even; PinHeader_2x10_P2.54mm_Vertical
J3, J5: Conn_02x03_Odd_Even; PinHeader_2x03_P2.54mm_Vertical
J4: DB15_Female_HighDensity; DSUB-15-HD_Female_Horizontal_P2.29x1.98mm_EdgePinOffset8.35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
JP1, JP2, JP3: SolderJumper_2_Open; SolderJumper-2_P1.3mm_Open_RoundedPad1.0x1.5mm
R1, R2, R3: 10k; R_Axial_DIN0207_L6.3mm_D2.5mm_P7.62mm_Horizontal
R4: 220; R_Axial_DIN0207_L6.3mm_D2.5mm_P7.62mm_Horizontal
U1: ATmega328-PU; DIP-28_W7.62mm
U2: LCC110; DIP-8_W7.62mm
Y1: Crystal; Crystal_HC49-U_Vertical

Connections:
/5V_TRICKLE: C3.1, D1.2, J2.6, J3.2, R1.2, R3.1, U2.5
/-10V: J1.3, J2.8
/BLUE: J2.13, J4.3
/COMPUTER_5V: D2.2, J4.9
/COMPUTER_SCL: J5.2, JP2.2, U1.28
/COMPUTER_SDA: J5.1, JP1.2, U1.27
/DCO: J1.5, J2.5
/GREEN: J2.15, J4.2
/H_SYNC: J2.9, J4.13
/IVAD_SCL: J2.2, U1.11
/IVAD_SDA: J2.1, U1.6
/LINE_SENSE: J1.2, J2.19
/LPIACT:L1_LP: J1.6, J2.10, J2.12, U2.6, U2.7
/MISO: J3.1, U1.18
/MOSI: J3.4, U1.17
/PB0: J5.4, U1.14
/PB1: J5.6, U1.15
/PROT: J1.4, J2.7, R2.2
/PWR_BTN: J1.1, R1.1, U1.5
/RED: J2.17, J4.1
/SCK: J3.3, U1.19
/SERIAL_RX: J5.3, U1.2
/SERIAL_TX: J5.5, U1.3
/V_SYNC: J2.11, J4.14, JP3.2
/~RESET: J3.5, R3.2, U1.1
GND: C1.1, C2.2, C3.2, H1.1, H2.1, J2.3, J2.4, J2.14, J2.16, J2.18, J2.20, J3.6, J4.5, J4.6, J4.7, J4.8, J4.10, R2.1, R4.1, U1.8, U1.22, U2.8
unnamed: C1.2, U1.9, Y1.1
unnamed: C2.1, U1.10, Y1.2
unnamed: D1.1, D2.1, U1.7, U1.20
unnamed: J4.12, JP1.1
unnamed: J4.15, JP2.1
unnamed: JP3.1, U1.16
unnamed: R4.2, U2.3
unnamed: U1.13, U2.2

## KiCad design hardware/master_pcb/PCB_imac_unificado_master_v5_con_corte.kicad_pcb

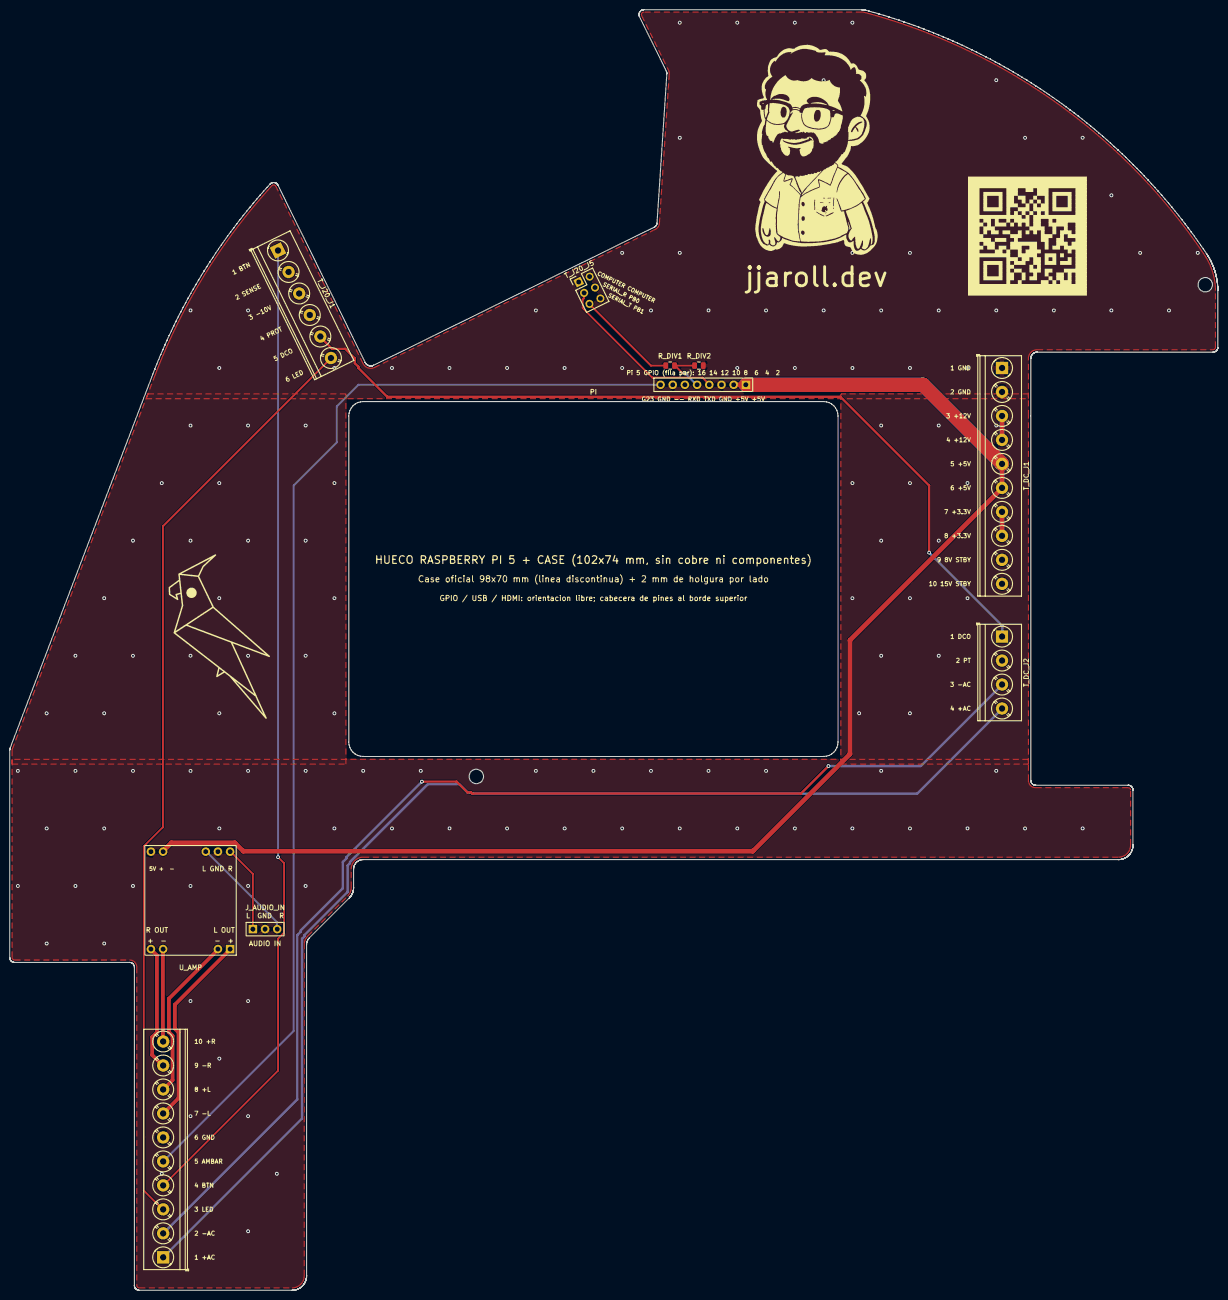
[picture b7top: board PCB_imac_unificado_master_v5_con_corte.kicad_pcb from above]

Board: 2 copper layers, 251.9 x 267.0 mm, 17 parts (0 on the bottom side), 19 nets.

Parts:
H_BASE_A: Tornillo a la base M3; MountingHole_3.0mm
H_BASE_B: Tornillo a la base M3; MountingHole_3.0mm
J_AUDIO_IN: Entrada audio L/GND/R; AudioIn_1x03_P2.54
J_PI_GPIO: GPIO Pi 5 pines 2-16 (fila par); Pi_GPIO_EvenRow_1x08_P2.54
LOGO_AVATAR: LOGO_AVATAR
LOGO_LORO: LOGO_LORO
LOGO_QR: LOGO_QR
LOGO_TEXTO: LOGO_TEXTO
PI: Hueco Raspberry Pi 5 con case (102x74); RaspberryPi5_Case_Hueco
R_DIV1: 1k; R_0805_2012Metric
R_DIV2: 2k; R_0805_2012Metric
T_DC_J1: Screw_Terminal_01x10; TerminalBlock_Phoenix_PT-1,5-10-5.0-H_1x10_P5.00mm_Horizont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
T_DC_J2: Screw_Terminal_01x04; TerminalBlock_Phoenix_PT-1,5-4-5.0-H_1x04_P5.00mm_Horizontal
T_J20_J1: Screw_Terminal_01x06; TerminalBlock_Phoenix_PT-1,5-6-5.0-H_1x06_P5.00mm_Horizontal
T_J20_J5: Conn_02x03_Odd_Even; PinHeader_2x03_P2.54mm_Vertical
T_J22_J2: Screw_Terminal_01x10; TerminalBlock_Phoenix_PT-1,5-10-5.0-H_1x10_P5.00mm_Horizont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
U_AMP: PAM8403 (modulo 19.05x22.86 mm, pines 2.54); PAM8403_Module_PinPads

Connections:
/+3.3V: T_DC_J1.7, T_DC_J1.8
/+5V: J_PI_GPIO.2, J_PI_GPIO.4, T_DC_J1.5, T_DC_J1.6, U_AMP.8
/+12V: T_DC_J1.3, T_DC_J1.4
/+AC: T_DC_J2.4, T_J22_J2.1
/+LEFT_SPEAKER: T_J22_J2.8, U_AMP.2
/+RIGHT_SPEAKER: T_J22_J2.10, U_AMP.3
/-AC: T_DC_J2.3, T_J22_J2.2
/-LEFT_SPEAKER: T_J22_J2.7, U_AMP.1
/-RIGHT_SPEAKER: T_J22_J2.9, U_AMP.4
/AUDIO_L: J_AUDIO_IN.1, U_AMP.5
/AUDIO_R: J_AUDIO_IN.3, U_AMP.7
/DCO: T_DC_J2.1, T_J20_J1.5
/LPIACT:L1_LP: T_J20_J1.6, T_J22_J2.3
/PI_GPIO23_AMBER: J_PI_GPIO.16, T_J22_J2.5
/PI_RXD: J_PI_GPIO.10, R_DIV1.2, R_DIV2.1
/POWER_BUTTON: T_J20_J1.1, T_J22_J2.4
/SERIAL_RX: J_PI_GPIO.8, T_J20_J5.3
/SERIAL_TX: R_DIV1.1, T_J20_J5.5
GND: J_AUDIO_IN.2, J_PI_GPIO.6, J_PI_GPIO.14, R_DIV2.2, T_DC_J1.1, T_DC_J1.2, T_J22_J2.6, U_AMP.6, U_AMP.9

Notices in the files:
README.md:
Bezel: CC BY-NC 4.0
hardware/placas_individuales/DownConverter/imac_g3_down_converter_board_adapter_es.kicad_pcb:
Original: qbancoffee/imac_g3_ivad_board_init (LGPL-3.0)
hardware/placas_individuales/J22_frontal_audio/imac_g3_slot_loading_J22_adapter_board_es.kicad_pcb:
Original: qbancoffee (LGPL-3.0) - Traduccion y firma: JJaroll.dev
